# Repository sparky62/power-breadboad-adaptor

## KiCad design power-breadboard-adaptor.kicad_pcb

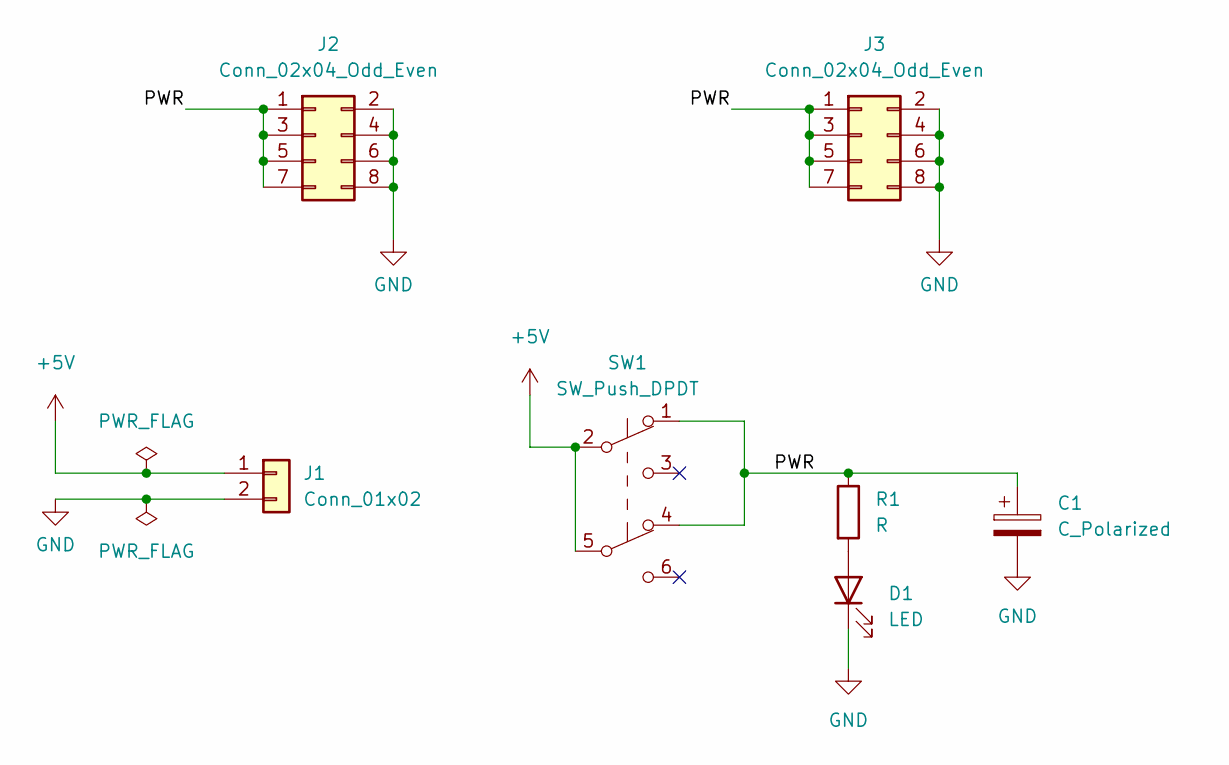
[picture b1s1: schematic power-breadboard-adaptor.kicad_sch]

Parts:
C1: C_Polarized; CP_Radial_D5.0mm_P2.00mm
D1: LED; LED_D5.0mm
J1: Conn_01x02; TerminalBlock_Altech_AK300-2_P5.00mm
J2, J3: Conn_02x04_Odd_Even; PinHeader_2x04_P2.54mm_Vertical
R1: R; R_Axial_DIN0204_L3.6mm_D1.6mm_P5.08mm_Horizontal
SW1: SW_Push_DPDT; SW_E-Switch_EG1271_DPDT

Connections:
+5V: J1.1, SW1.2 (B), SW1.5 (B)
/PWR: C1.1, J2.1, J2.3, J2.5, J2.7, J3.1, J3.3, J3.5, J3.7, R1.1, SW1.1 (A), SW1.4 (A)
GND: C1.2, D1.1 (K), J1.2, J2.2, J2.4, J2.6, J2.8, J3.2, J3.4, J3.6, J3.8
unnamed: D1.2 (A), R1.2

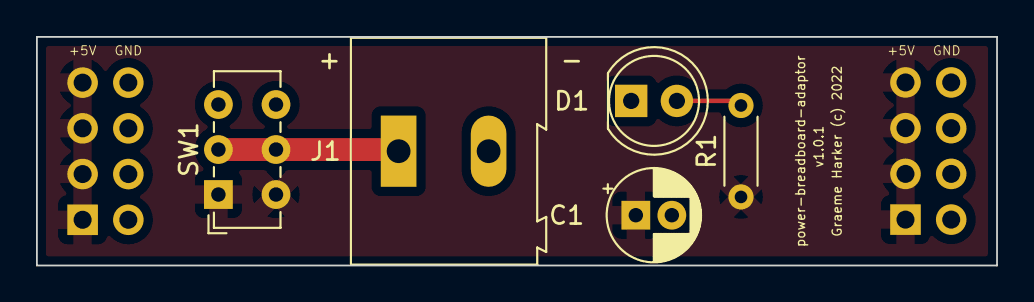
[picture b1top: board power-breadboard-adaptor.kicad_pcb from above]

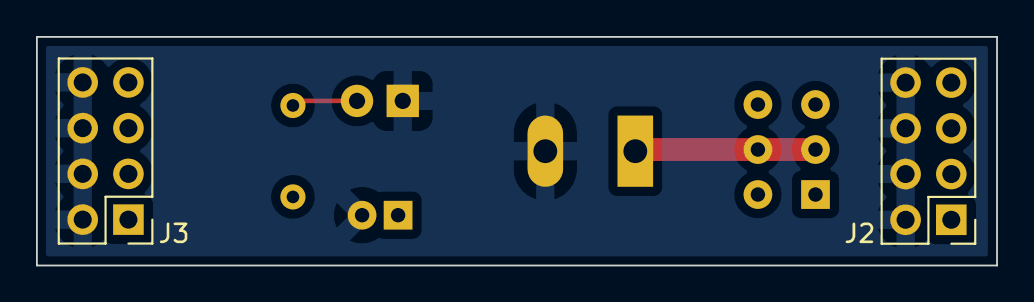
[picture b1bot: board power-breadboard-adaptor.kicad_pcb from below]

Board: 2 copper layers, 53.3 x 12.7 mm, 7 parts (2 on the bottom side), 4 nets.

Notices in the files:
power-breadboard-adaptor.kicad_pcb:
Graeme Harker (c) 2022
